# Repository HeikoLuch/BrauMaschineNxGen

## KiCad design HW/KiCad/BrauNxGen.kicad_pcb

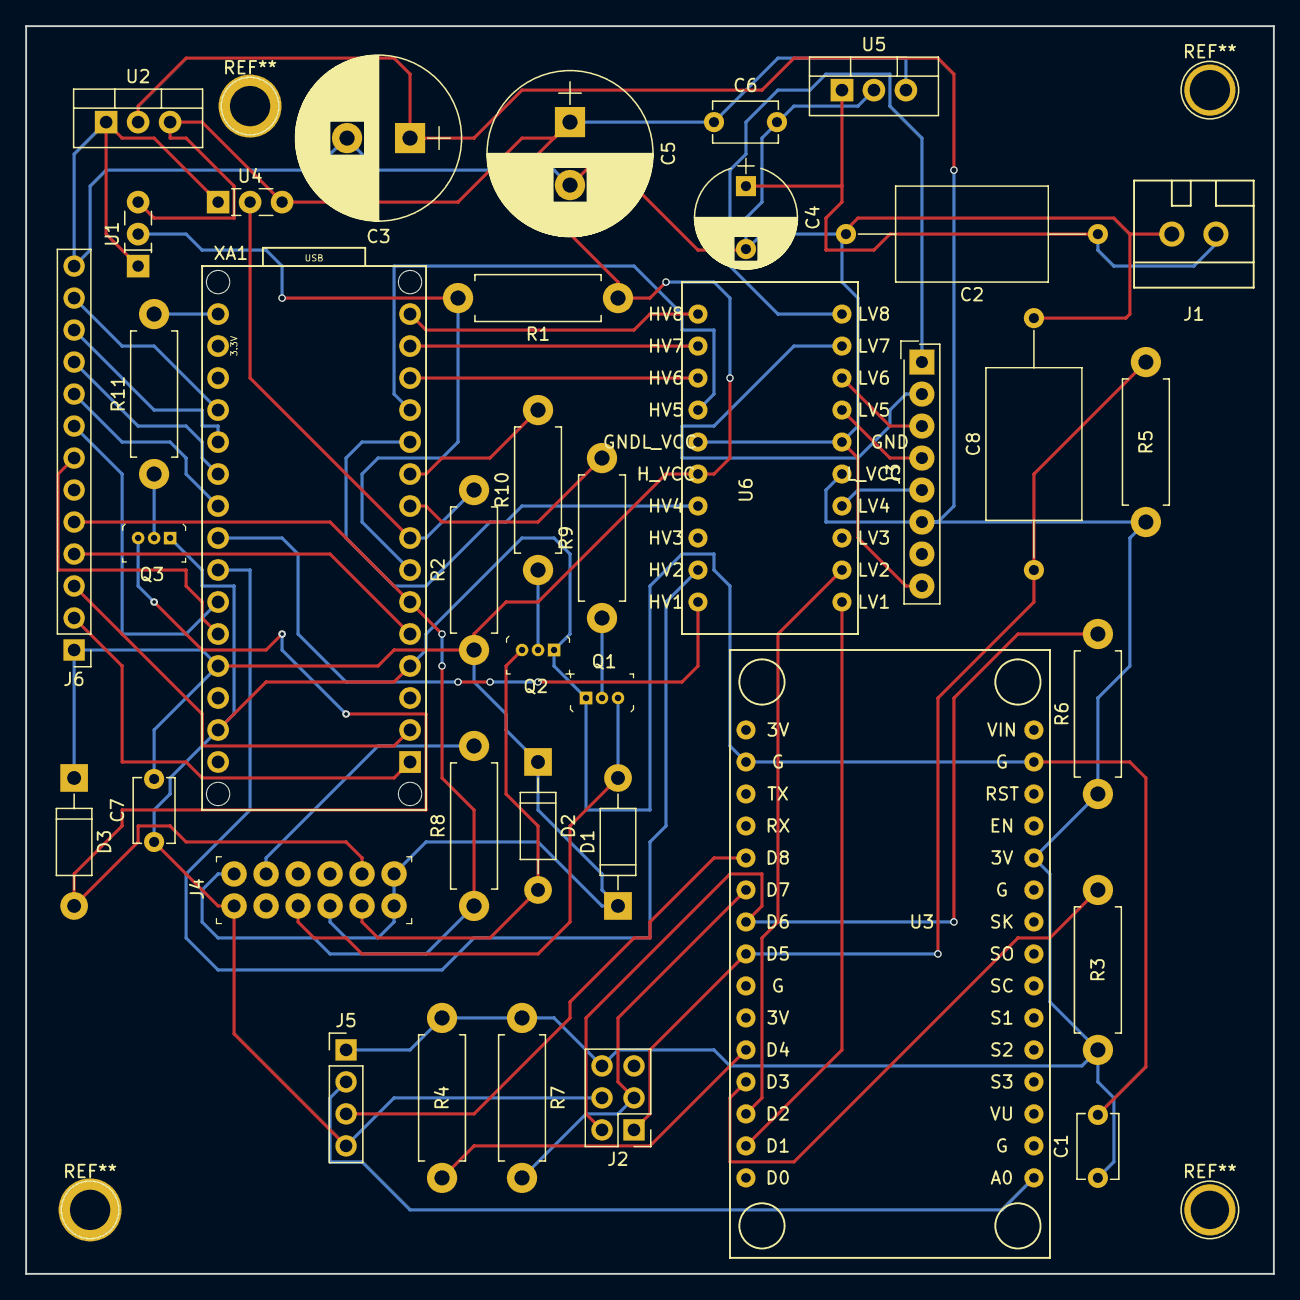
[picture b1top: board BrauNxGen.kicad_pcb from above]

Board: 2 copper layers, 99.1 x 99.1 mm, 38 parts (0 on the bottom side), 47 nets.

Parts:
C1, C6, C7: 100nF; C_Disc_D5.1mm_W3.2mm_P5.00mm
C2: 220nF; C_Axial_L12.0mm_D7.5mm_P20.00mm_Horizontal
C3: 470µF; CP_Radial_D13.0mm_P5.00mm
C4: 100µF; CP_Radial_D8.0mm_P5.00mm
C5: 220µF; CP_Radial_D13.0mm_P5.00mm
C8: 10nF; C_Axial_L12.0mm_D7.5mm_P20.00mm_Horizontal
D1, D2, D3: 1N4007; D_DO-41_SOD81_P10.16mm_Horizontal
J1: Conn_01x02; WAGO_734_2pin_Straight
J2: Rotary; Pin_Header_Straight_2x03_Pitch2.54mm
J3: LCD; SL-108-X-XX_1x08
J4: Buzzer & Relais; PinHeader_6x2_P2.54mm_Vertical
J5: Conn_01x04_Male; Pin_Header_Straight_1x04_Pitch2.54mm
J6: Conn_01x13_Male; Pin_Header_Straight_1x13_Pitch2.54mm
Q1, Q2, Q3: 2N2222; TO-92-3
R1, R2: 10k; R_Axial_DIN0411_L9.9mm_D3.6mm_P12.70mm_Horizontal
R3, R4, R5, R6, R7: 4,7k; R_Axial_DIN0411_L9.9mm_D3.6mm_P12.70mm_Horizontal
R8: 100R; R_Axial_DIN0411_L9.9mm_D3.6mm_P12.70mm_Horizontal
R9, R10, R11: 1k; R_Axial_DIN0411_L9.9mm_D3.6mm_P12.70mm_Horizontal
U1, U4: DS18B20_; LED_Rectangular_W5.0mm_H2.0mm-3pins
U2: LD1117V33; TO-220-3_Vertical
U3: NodeMCU1.0(ESP-12E); NodeMCU1.0_Small
U5: V7805-1000; TO-220-3_Vertical
U6: 8-CH_LevelShifter; Level-Shifter_8_Channels
XA1: Arduino_Nano_Socket

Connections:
+3V3: C1.1, C3.1, J2.6, J3.6, J5.1, R3.1, R4.1, R5.1, R6.1, R7.1, U2.2, U3.11, U6.5
+5V: C5.1, C6.1, C7.2, D1.1, D2.1, D3.1, J4.4, J4.6, J4.7, J6.1, R1.1, R2.1, U1.3, U2.3, U4.3, U5.3, U6.16, XA1.5V
+12V: C2.1, C4.1, J1.1, U5.1
A0: J6.12, XA1.A0
A1: J6.11, XA1.A1
A2: J6.10, XA1.A2
A3: J6.9, XA1.A3
A6: J6.8, XA1.A6
A7: J6.7, XA1.A7
D0: J6.3, XA1.D0
D1: J6.2, XA1.D1
D2: J6.4, XA1.D2
D3: J4.12, J6.5, R8.1, XA1.D3
D4: R1.2, U1.2, XA1.D4
D5: R2.2, U4.2, XA1.D5
D6: R9.2, XA1.D6
D7: R10.2, XA1.D7
D13: R11.2, XA1.D13
E_A0: J5.2, U3.1
E_D8: J5.3, U3.20
GND: C1.2, C2.2, C3.2, C4.2, C5.2, C6.2, C7.1, C8.2, J1.2, J2.4, J3.8, J4.1, J5.4, J6.13, Q1.1, Q2.1, Q3.1, U1.1, U2.1, U3.14, U3.17, U4.1, U5.2, U6.6, U6.15, XA1.GND1, XA1.GND2
unnamed: C8.1, J2.1, R5.2, U3.23
unnamed: J2.2, R6.2, U3.22
unnamed: J2.3, R7.2, U3.21
unnamed: J3.1, U6.10
unnamed: J3.2, U6.9
unnamed: J3.3, U6.8
unnamed: J3.4, U6.7
unnamed: J3.5, U6.4
unnamed: J4.11, R8.2
unnamed: Q1.2, R9.1
unnamed: Q2.2, R10.1
unnamed: Q3.2, R11.1
unnamed: R3.2, U3.27
unnamed: R4.2, U3.26
unnamed: U3.28, U6.2
unnamed: U3.29, U6.1
unnamed: U6.11, XA1.D12
unnamed: U6.12, XA1.D11
unnamed: U6.13, XA1.D10
unnamed: U6.14, XA1.D9
unnamed: U6.17, XA1.D8
unnamed: U6.19, XA1.A5
unnamed: U6.20, XA1.A4
R_LAUT_2: D2.2, J4.5, Q2.3
R_PUMP_2: D3.2, J4.8, Q3.3
R_SUD_2: D1.2, J4.3, Q1.3

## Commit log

2018-09-10 HW Layout added
